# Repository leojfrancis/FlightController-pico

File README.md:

## Flight Controller

For building the project run make in the parent directory
```
make help
```

Do this for adding support for lora need to work on it 
```
git clone --recurse-submodules https://github.com/sandeepmistry/pico-lorawan.git 
```

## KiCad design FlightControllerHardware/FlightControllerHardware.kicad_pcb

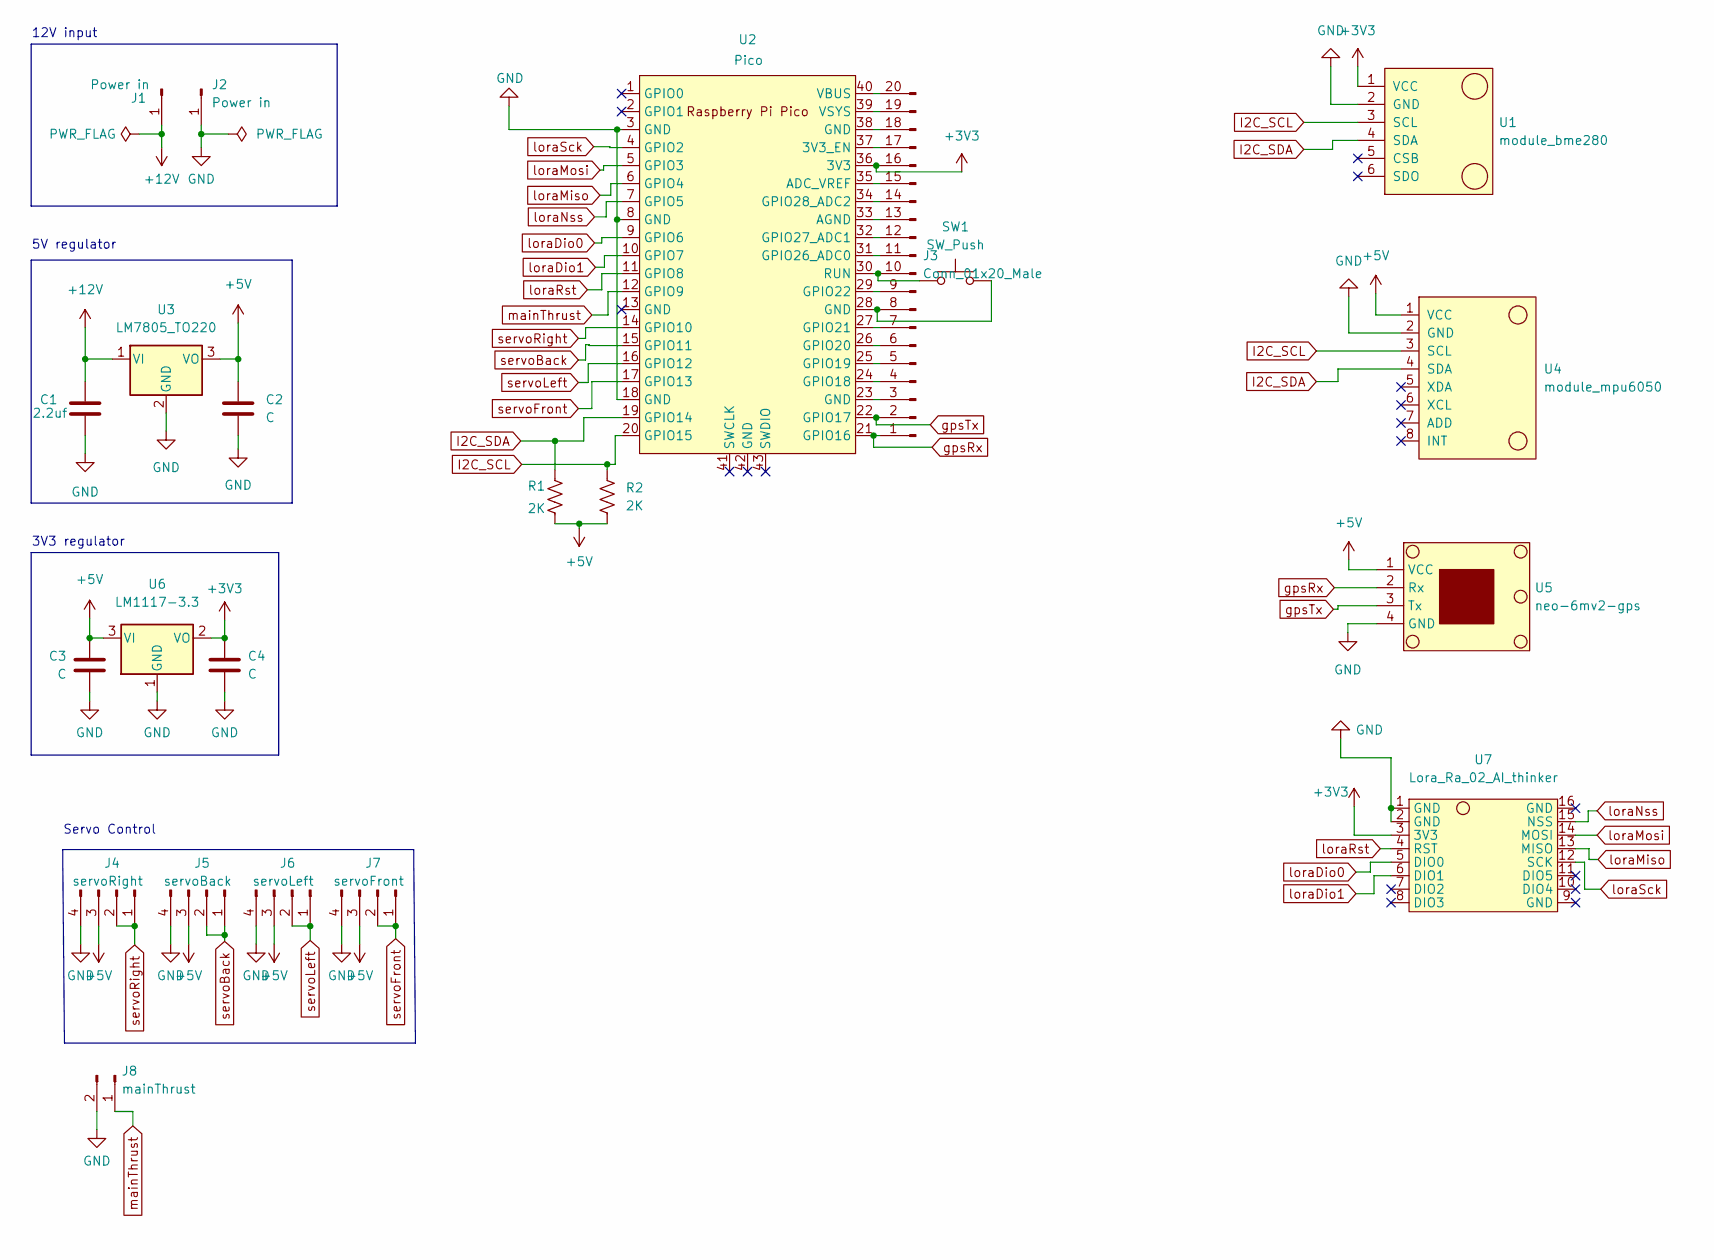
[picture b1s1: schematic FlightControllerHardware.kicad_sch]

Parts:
C1: 2.2uf; C_Axial_L3.8mm_D2.6mm_P7.50mm_Horizontal
C2, C3, C4: C; C_Axial_L3.8mm_D2.6mm_P7.50mm_Horizontal
J1, J2: Power in; Pin_D1.3mm_L11.0mm_LooseFit
J3: Conn_01x20_Male; PinHeader_1x20_P2.54mm_Vertical
J4: servoRight; JST_EH_B4B-EH-A_1x04_P2.50mm_Vertical
J5: servoBack; JST_EH_B4B-EH-A_1x04_P2.50mm_Vertical
J6: servoLeft; JST_EH_B4B-EH-A_1x04_P2.50mm_Vertical
J7: servoFront; JST_EH_B4B-EH-A_1x04_P2.50mm_Vertical
J8: mainThrust; JST_EH_B2B-EH-A_1x02_P2.50mm_Vertical
R1, R2: 2K; R_Axial_DIN0204_L3.6mm_D1.6mm_P5.08mm_Horizontal
SW1: SW_Push; SW_PUSH_6mm
U1: module_bme280
U2: Pico; RPi_Pico_SMD_TH
U3: LM7805_TO220; TO-220-3_Vertical
U4: module_mpu6050
U5: neo-6mv2-gps; gps_ublox_6mv2
U6: LM1117-3.3; TO-220-3_Vertical
U7: Lora_Ra_02_AI_thinker; Lora Ra 02 AI Thinker

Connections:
+12V: C1.2, J1.1, U3.1 (VI)
GND: C1.1, C2.2, C3.1, C4.1, J2.1, J4.4, J5.4, J6.4, J7.4, J8.2, U1.2 (GND), U2.3 (GND), U2.8 (GND), U2.18 (GND), U3.2 (GND), U4.2 (GND), U5.4 (GND), U6.1 (GND), U7.1 (GND), U7.2 (GND)
I2C_SCL: R2.2, U1.3 (SCL), U2.20 (GPIO15), U4.3 (SCL)
I2C_SDA: R1.1, U1.4 (SDA), U2.19 (GPIO14), U4.4 (SDA)
unnamed: J3.3, U2.23 (GND)
unnamed: J3.4, U2.24 (GPIO18)
unnamed: J3.5, U2.25 (GPIO19)
unnamed: J3.6, U2.26 (GPIO20)
unnamed: J3.7, U2.27 (GPIO21)
unnamed: J3.8, SW1.2, U2.28 (GND)
unnamed: J3.9, U2.29 (GPIO22)
unnamed: J3.10, SW1.1, U2.30 (RUN)
unnamed: J3.11, U2.31 (GPIO26_ADC0)
unnamed: J3.12, U2.32 (GPIO27_ADC1)
unnamed: J3.13, U2.33 (AGND)
unnamed: J3.14, U2.34 (GPIO28_ADC2)
unnamed: J3.15, U2.35 (ADC_VREF)
unnamed: J3.17, U2.37 (3V3_EN)
unnamed: J3.18, U2.38 (GND)
unnamed: J3.19, U2.39 (VSYS)
unnamed: J3.20, U2.40 (VBUS)
gpsRx: J3.1, U2.21 (GPIO16), U5.2 (Rx)
gpsTx: J3.2, U2.22 (GPIO17), U5.3 (Tx)
loraDio0: U2.9 (GPIO6), U7.5 (DIO0)
loraDio1: U2.10 (GPIO7), U7.6 (DIO1)
loraMiso: U2.6 (GPIO4), U7.13 (MISO)
loraMosi: U2.5 (GPIO3), U7.14 (MOSI)
loraNss: U2.7 (GPIO5), U7.15 (NSS)
loraRst: U2.11 (GPIO8), U7.4 (RST)
loraSck: U2.4 (GPIO2), U7.12 (SCK)
mainThrust: J8.1, U2.12 (GPIO9)
servoBack: J5.1, J5.2, U2.15 (GPIO11)
servoFront: J7.1, J7.2, U2.17 (GPIO13)
servoLeft: J6.1, J6.2, U2.16 (GPIO12)
servoRight: J4.1, J4.2, U2.14 (GPIO10)

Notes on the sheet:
5V regulator
12V input
3V3 regulator
Servo Control

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
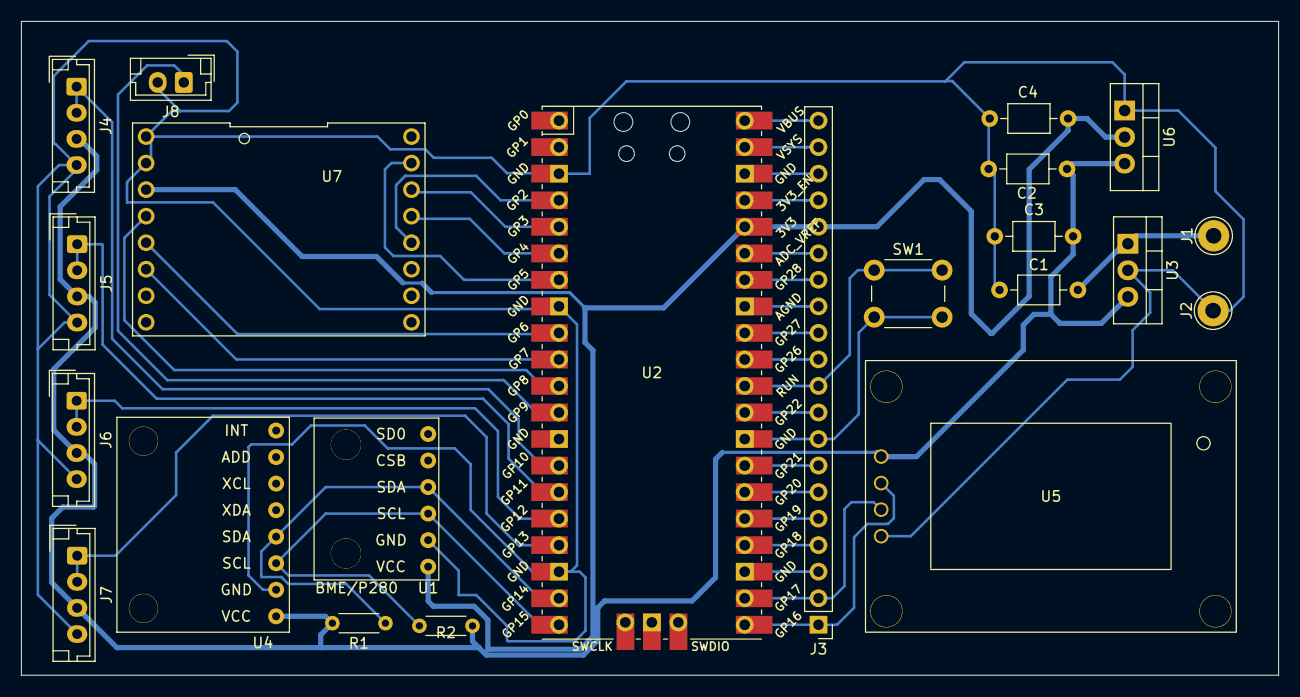
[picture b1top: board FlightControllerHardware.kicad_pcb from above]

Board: 2 copper layers, 120.3 x 62.6 mm, 22 parts (0 on the bottom side), 36 nets.

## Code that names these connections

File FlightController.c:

#include <stdio.h>
#include "pico/stdlib.h"
#include "hardware/pwm.h"
// #include "hardware/spi.h"
// #include "hardware/i2c.h"
// #include "hardware/pio.h"
// #include "hardware/timer.h"

// SPI Defines
// We are going to use SPI 0, and allocate it to the following GPIO pins
// Pins can be changed, see the GPIO function select table in the datasheet for information on GPIO assignments
#define SPI_PORT spi0
#define PIN_MISO 16
#define PIN_CS 17
#define PIN_SCK 18
#define PIN_MOSI 19

// I2C defines
// This example will use I2C0 on GPIO8 (SDA) and GPIO9 (SCL) running at 400KHz.
// Pins can be changed, see the GPIO function select table in the datasheet for information on GPIO assignments
#define I2C_PORT i2c0
#define I2C_SDA 8
#define I2C_SCL 9

// PWM defines
#define PWM_PIN 2
#define PWM_CLC "8ns"
uint32_t wrap = 16;

long map(long x, long in_min, long in_max, long out_min, long out_max)
{
    return (x - in_min) * (out_max - out_min) / (in_max - in_min) + out_min;
}

uint32_t pwm_set_freq_duty(uint slice_num,
                           uint chan, uint32_t f, int d)
{
    uint32_t clock = 125000000;
    uint32_t divider16 = clock / f / 4096 +
                         (clock % (f * 4096) != 0); // Understand whats happining in the calculation for clk_divider.
    if (divider16 / 16 == 0)
        divider16 = 16;
    wrap = clock * 16 / divider16 / f - 1;
    pwm_set_clkdiv_int_frac(slice_num, divider16 / 16,
                            divider16 & 0xF);
    pwm_set_wrap(slice_num, wrap);
    pwm_set_chan_level(slice_num, chan, wrap * d / 100);
    return wrap;
}

uint32_t pwm_set_duty(uint slice_num, uint chan, int d)
{
    pwm_set_chan_level(slice_num, chan, wrap * d / 100);
    return wrap;
}

int main()
{
    stdio_init_all();

    gpio_set_function(PWM_PIN, GPIO_FUNC_PWM);
    uint slice_num = pwm_gpio_to_slice_num(PWM_PIN);
    pwm_set_freq_duty(slice_num, PWM_CHAN_A, 50, 5);
    pwm_set_enabled(slice_num, true);
    sleep_ms(10000);
    pwm_set_duty(slice_num, PWM_CHAN_A, 7);

    while (1)
    {
    }
    return true;
}

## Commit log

2022-06-09 added base repo
2022-06-26 basic pid integrated with libs
2022-06-28 redefined motor, servo lib and added readme
2022-06-30 semi calibrated and updated motor files
2022-07-01 added hardware
2022-07-03 finished routing
2022-07-04 updated pcb to backtraces and removed vias
2022-07-07 temp changes for thrust control, cut off at 45 for servos
